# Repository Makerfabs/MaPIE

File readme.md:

# Makerfabs MaPIE

```c++
/*
Version:		V2.1
Author:			Vincent
Create Date:	2022/6/2
Note:

2022/12/30		V2.1 Edit wiki link
2022/11/23		V2.0 Add MaPIE 0.96 OLED
2022/6/2		V1.0 Create Project
			
*/
```

[toc]

# Makerfabs

[Makerfabs home page](https://www.makerfabs.com/)

[Makerfabs Wiki](https://wiki.makerfabs.com/)

# What is MaPIE 

MaPIE is Makerfabs development board product line based on RP2040.

RP2040 is an MCU developed by Raspberry PI and can support Arduino, MicroPython and C_SDK development.

Compared to the traditional Arduino UNO 328P, it has better performance and more hardware resources. 

## MaPIE List

| Name                                                         | Status      |
| ------------------------------------------------------------ | ----------- |
| [MaPIE LoRa RP2040](MaPIE_Lora/)                     | **Already** |
| [MaPIE 0.96 OLED](MaPIE-0.96-OLED/) | **Already** |
|                                                              |             |

# How To Use

## Complier Option

**If you have any questions，such as how to install the development board, how to download the code, how to install the library. Please refer to :[Makerfabs_FAQ](https://github.com/Makerfabs/Makerfabs_FAQ)**

- Please disconnect from the electrical equipment before burning!
- Do not burn with alternating current!
- Open Arduino IDE
- Open boards Manager, search "RP2040"
- Install board:  Arduino Mbed OS RP2040 Boards(Version 3.1.1)

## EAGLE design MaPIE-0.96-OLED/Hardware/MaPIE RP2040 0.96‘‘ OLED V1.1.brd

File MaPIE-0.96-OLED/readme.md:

# MaPIE RP2040 0.96‘‘ OLED

```c++
/*
Version:		V1.0
Author:			Vincent
Create Date:	2022/11/23
Note:
	
*/
```

[toc]

# Makerfabs

[Makerfabs home page](https://www.makerfabs.com/)

[Makerfabs Wiki](https://wiki.makerfabs.com/)

# MaPIE RP2040 0.96‘‘ OLED

## Intruduce

Product Link ：[MaPIE RP2040 0.96" OLED](https://www.makerfabs.com/mapie-rp2040-0-96-inch-oled.html) 

Wiki Link : [MaPIE RP2040 0.96" OLED](https://wiki.makerfabs.com/MaPIE_RP2040_0.96_OLED.html) 

This MaPIE RP2040 OLED is a low-cost, high-performance Pico-like MCU board with flexible digital interfaces. It is based on Raspberry Pi's RP2040 microcontroller chip, as same as that on Raspberry Pi Pico. Users can develop applications based on Raspberry Pi's C/C++ SDK, or the MicroPython/ Arduino.

## Feature

- P2040 microcontroller Dual-core Arm Cortex M0+ processor, flexible clock running up to 133 MHz
- 16MB on-board Flash memory
- USB-C connector
- 0.96" 128*64 OLED
- Lithium battery connector/ charge
- Same pins breakout as Pico: 26 x multi-function GPIO pins; 2 x SPI, 2 x I2C, 2 x UART, 3 x 12-bit ADC, 16 x controllable PWM channels

### Front:

### Back:

# Arduino

## Compiler Options

**If you have any questions，such as how to install the development board, how to download the code, how to install the library. Please refer to :[Makerfabs_FAQ](https://github.com/Makerfabs/Makerfabs_FAQ)**

- Install board : Arduino Mbed OS RP2040 Boards
- Install library : Adafruit_GFX library.
- Install library : Adafruit_SSD1306 library.

Modify pins_Arduino.h

```c++
//variants\RASPBERRY_PI_PICO\pins_arduino.h

// Wire
// #define PIN_WIRE_SDA        (4u)
// #define PIN_WIRE_SCL        (5u)

// Change By Vincent
#define PIN_WIRE_SDA        (6u)
#define PIN_WIRE_SCL        (7u)
```

**First time upload need hold boot button when restart.**

# MicroPython

## Burn Fireware

Download MicroPython from the Raspberry PI Pico's official tutorial:

[https://www.raspberrypi.com/products/raspberry-pi-pico/](https://www.raspberrypi.com/products/raspberry-pi-pico/)

## Upload Code

Connect MaPie to PC.

Use Thonny IDE, upload all file to MaPie.

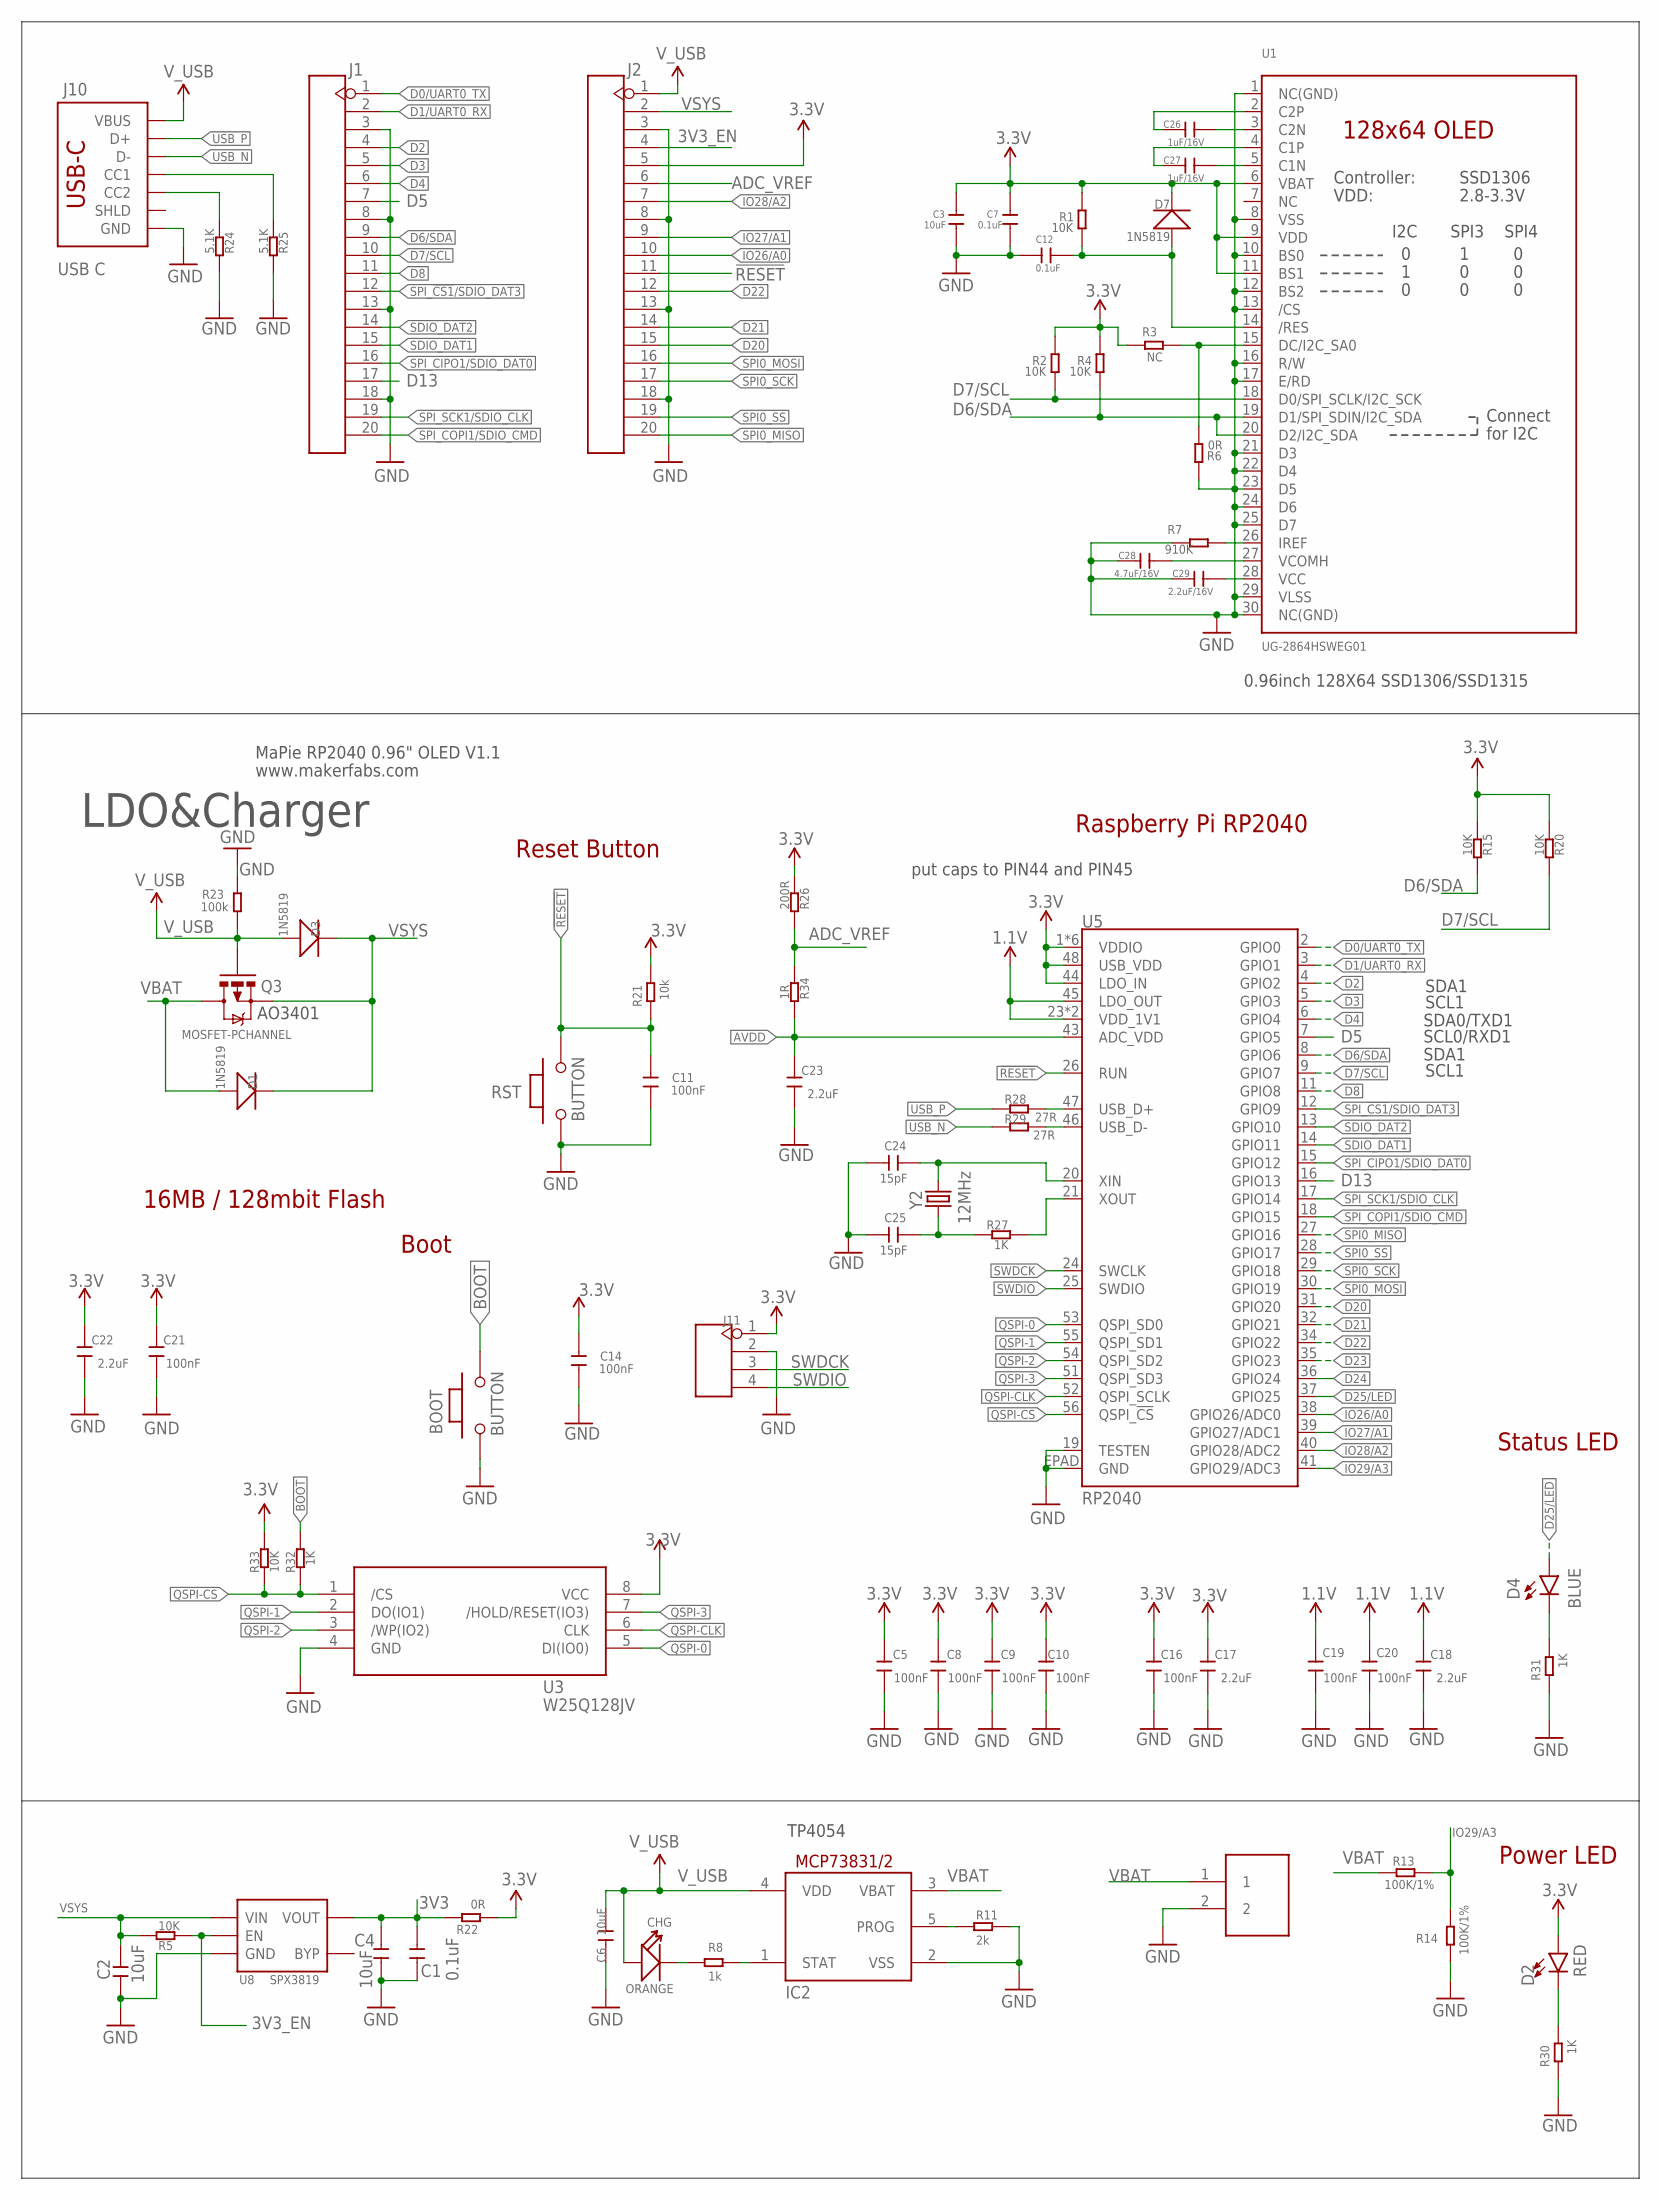
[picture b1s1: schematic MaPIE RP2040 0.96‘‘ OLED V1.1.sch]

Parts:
BAT: PH2.0-2P-90-DIP
BOOT: BUTTON; 157SW
C1, C7, C12: 0.1uF; C0603
C2, C3, C4, C6: 10uF; C0603
C5, C8, C9, C10, C11, C14, C16, C19, C20, C21: 100nF; C0603
C17, C18, C22, C23: 2.2uF; C0603
C24, C25: 15pF; C0603
C26, C27: 1uF/16V; C0603
C28: 4.7uF/16V; C0603
C29: 2.2uF/16V; C0603
CHG: ORANGE; D0603
D1, D3, D7: 1N5819; SOD323
D2: RED; LED-0603
D4: BLUE; LED-0603
IC2: MCP73831/OT; SOT23-5L
J1, J2: HEADER-20P-2.54; 20P-2.54
J10: USB C; USB-C-16P-4LAYER-ISOLATED
J11: HEADER-4P-60/35MILROUND; 4P-65/35ROUND
Q3: MOSFET-PCHANNEL; SOT23-3
R1, R2, R4, R5, R15, R20, R33: 10K; 0603
R3: NC; 0603
R6, R22: 0R; 0603
R7: 910K; 0603
R8: 1k; 0603
R11: 2k; 0603
R13, R14: 100K/1%; 0603
R21: 10k; 0603
R23: 100k; 0603
R24, R25: 5.1K; 0603
R26: 200R; 0603
R27, R30, R31, R32: 1K; 0603
R28, R29: 27R; 0603
R34: 1R; 0603
RST: BUTTON; 157SW
U1: UG-2864HSWEG01; UG-2864HSWEG01_0.96IN_WRAPAROUND
U3: W25Q128JV; SOIC-8-208MIL
U5: RP2040; QFN-56
U8: SPX3819; SOT23-5
Y2: 12MHz; CRYSTAL-SMD-2X2.5MM

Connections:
1.1V: C18.2, C19.2, C20.2, U5.23 (VDD_1V1), U5.45 (LDO_OUT), U5.50 (VDD_1V1)
3.3V: C3.1, C5.2, C7.1, C8.2, C9.2, C10.2, C14.2, C16.2, C17.2, C21.2, C22.2, D2.A, D7.-, J2.5, J11.1, R1.2, R2.2, R3.2, R4.2, R15.2, R20.2, R21.1, R22.1, R26.2, R33.1, U1.6 (VBAT), U1.9 (VDD), U1.11 (BS1), U3.8 (VCC), U5.1 (VDDIO), U5.10 (VDDIO), U5.22 (VDDIO), U5.33 (VDDIO), U5.42 (VDDIO), U5.44 (LDO_IN), U5.48 (USB_VDD), U5.49 (VDDIO)
3V3: C1.2, C4.2, R22.2, U8.5 (VOUT)
3V3_EN: J2.4, R5.2, U8.3 (EN)
!RESET!: C11.2, J2.11, R21.2, RST.2, U5.26 (RUN)
ADC_VREF: J2.6, R26.1, R34.2
AVDD: C23.2, R34.1, U5.43 (ADC_VDD)
BOOT: BOOT.2, R32.1
D0/UART0_TX: J1.1, U5.2 (GPIO0)
D1/UART0_RX: J1.2, U5.3 (GPIO1)
D2: J1.4, U5.4 (GPIO2)
D3: J1.5, U5.5 (GPIO3)
D4: J1.6, U5.6 (GPIO4)
D5: J1.7, U5.7 (GPIO5)
D6/SDA: J1.9, R4.1, R15.1, U1.19 (D1/SPI_SDIN/I2C_SDA), U1.20 (D2/I2C_SDA), U5.8 (GPIO6)
D7/SCL: J1.10, R2.1, R20.1, U1.18 (D0/SPI_SCLK/I2C_SCK), U5.9 (GPIO7)
D8: J1.11, U5.11 (GPIO8)
D13: J1.17, U5.16 (GPIO13)
D20: J2.15, U5.31 (GPIO20)
D21: J2.14, U5.32 (GPIO21)
D22: J2.12, U5.34 (GPIO22)
D23: U5.35 (GPIO23)
D24: U5.36 (GPIO24)
D25/LED: D4.A, U5.37 (GPIO25)
GND: BAT.2, BOOT.1, C1.1, C2.1, C3.2, C4.1, C5.1, C6.1, C7.2, C8.1, C9.1, C10.1, C11.1, C12.1, C14.1, C16.1, C17.1, C18.1, C19.1, C20.1, C21.1, C22.1, C23.1, C24.2, C25.2, C28.1, C29.1, IC2.2 (VSS), J1.3, J1.8, J1.13, J1.18, J2.3, J2.8, J2.13, J2.18, J10.GND, J10.GND2 (GND), J11.2, R6.2, R7.2, R11.2, R14.1, R23.2, R24.1, R25.1, R30.2, R31.2, RST.1, U1.1 (NC(GND)), U1.8 (VSS), U1.10 (BS0), U1.12 (BS2), U1.13 (/CS), U1.16 (R/W), U1.17 (E/RD), U1.21 (D3), U1.22 (D4), U1.23 (D5), U1.24 (D6), U1.25 (D7), U1.29 (VLSS), U1.30 (NC(GND)), U3.4 (GND), U5.19 (TESTEN), U5.EPAD (GND), U8.2 (GND)
IO26/A0: J2.10, U5.38 (GPIO26/ADC0)
IO27/A1: J2.9, U5.39 (GPIO27/ADC1)
IO28/A2: J2.7, U5.40 (GPIO28/ADC2)
IO29/A3: R13.1, R14.2, U5.41 (GPIO29/ADC3)
unnamed: C24.1, U5.20 (XIN), Y2.P3 (2)
unnamed: D4.C, R31.1
unnamed: R3.1, R6.1, U1.15 (DC/I2C_SA0)
unnamed: R27.1, U5.21 (XOUT)
unnamed: C28.2, U1.27 (VCOMH)
unnamed: C25.1, R27.2, Y2.P1 (1)
unnamed: D2.C, R30.1
unnamed: C29.2, U1.28 (VCC)
unnamed: R7.1, U1.26 (IREF)
unnamed: C26.2, U1.3 (C2N)
unnamed: J10.A5 (CC1), R25.2
unnamed: J10.B5 (CC2), R24.2
unnamed: C26.1, U1.2 (C2P)
unnamed: C27.1, U1.4 (C1P)
unnamed: C27.2, U1.5 (C1N)
unnamed: C12.2, D7.+, R1.1, U1.14 (/RES)
unnamed: CHG.-, R8.1
unnamed: IC2.1 (STAT), R8.2
unnamed: IC2.5 (PROG), R11.1
QSPI-0: U3.5 (DI(IO0)), U5.53 (QSPI_SD0)
QSPI-1: U3.2 (DO(IO1)), U5.55 (QSPI_SD1)
QSPI-2: U3.3 (/WP(IO2)), U5.54 (QSPI_SD2)
QSPI-3: U3.7 (/HOLD/RESET(IO3)), U5.51 (QSPI_SD3)
QSPI-CLK: U3.6 (CLK), U5.52 (QSPI_SCLK)
QSPI-CS: R32.2, R33.2, U3.1 (/CS), U5.56 (QSPI_!CS!)
SDIO_DAT1: J1.15, U5.14 (GPIO11)
SDIO_DAT2: J1.14, U5.13 (GPIO10)
SPI0_MISO: J2.20, U5.27 (GPIO16)
SPI0_MOSI: J2.16, U5.30 (GPIO19)
SPI0_SCK: J2.17, U5.29 (GPIO18)
SPI0_SS: J2.19, U5.28 (GPIO17)
SPI_!CS1!/SDIO_DAT3: J1.12, U5.12 (GPIO9)
SPI_CIPO1/SDIO_DAT0: J1.16, U5.15 (GPIO12)
SPI_COPI1/SDIO_CMD: J1.20, U5.18 (GPIO15)
SPI_SCK1/SDIO_CLK: J1.19, U5.17 (GPIO14)
SWDCK: J11.3, U5.24 (SWCLK)
SWDIO: J11.4, U5.25 (SWDIO)
USB_F_N: R29.1, U5.46 (USB_D-)
USB_F_P: R28.1, U5.47 (USB_D+)
USB_N: J10.A7 (D-), J10.B7 (D-), R29.2
USB_P: J10.A6 (D+), J10.B6 (D+), R28.2
VBAT: BAT.1, D1.+, IC2.3 (VBAT), Q3.3 (D), R13.2
VSYS: C2.2, D1.-, D3.-, J2.2, Q3.2 (S), R5.1, U8.1 (VIN)
V_USB: C6.2, CHG.+, D3.+, IC2.4 (VDD), J2.1, J10.VBUS1 (VBUS), J10.VBUS2 (VBUS), Q3.1 (G), R23.1

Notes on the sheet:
MaPie RP2040 0.96" OLED V1.1
www.makerfabs.com
TP4054
16MB / 128mbit Flash
Raspberry Pi RP2040
Reset Button
Status LED
Boot
Power LED
put caps to PIN44 and PIN45
SDA0/TXD1
SCL0/RXD1
SDA1
SCL1
LDO&Charger
AO3401
0.96inch 128X64 SSD1306/SSD1315

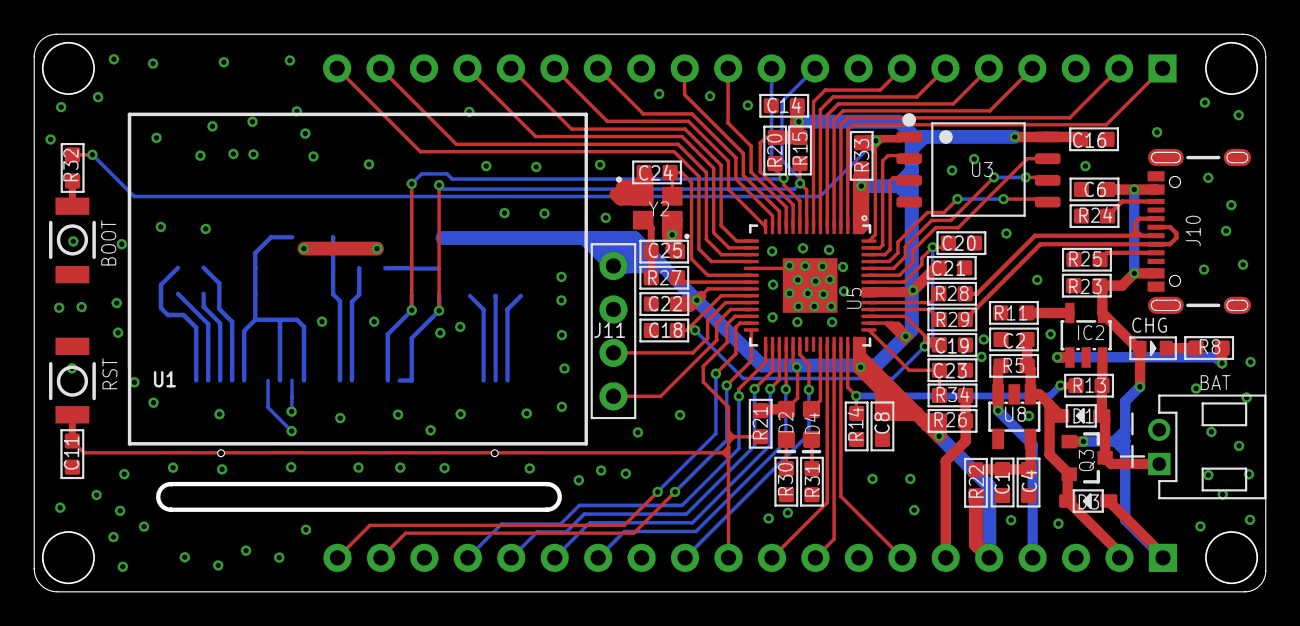
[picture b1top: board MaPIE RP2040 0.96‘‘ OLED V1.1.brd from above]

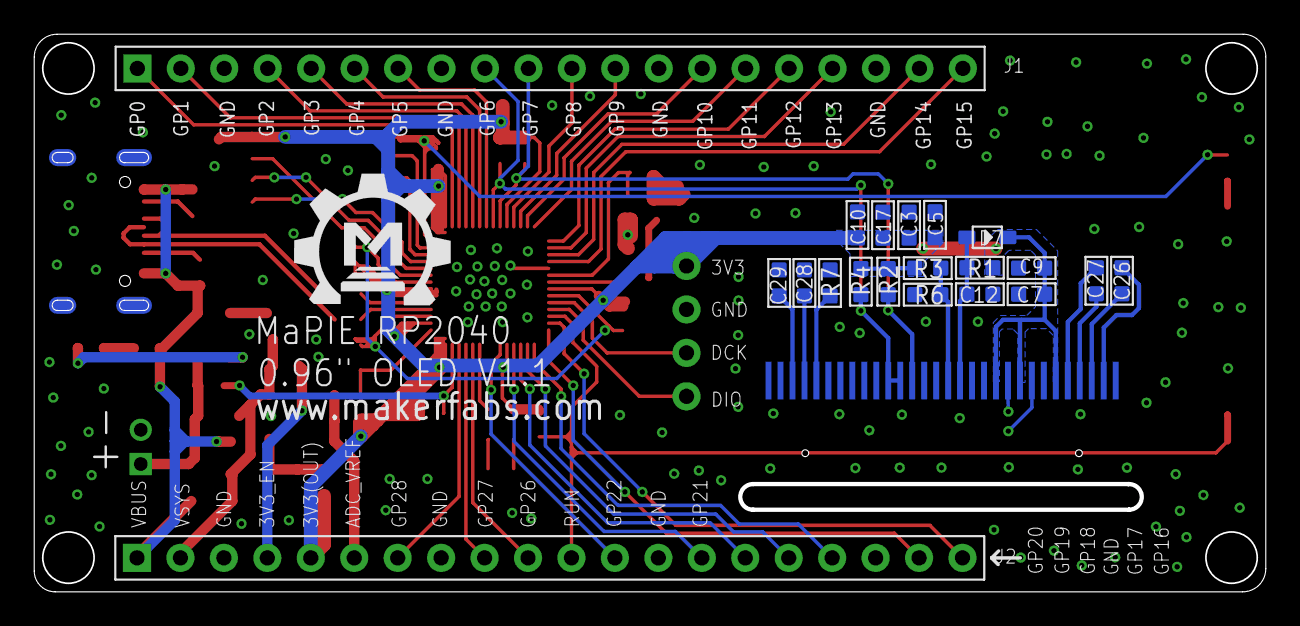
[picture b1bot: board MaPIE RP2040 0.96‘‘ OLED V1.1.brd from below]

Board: 2 copper layers, 71.7 x 32.3 mm, 75 parts (21 on the bottom side), 71 nets.

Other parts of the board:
U$1: MAKERFABS_0.3

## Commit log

2022-06-02 Create Project.
2022-06-05 Add compiled firmware
2022-06-16 Add MaPIE lora hardware
2022-11-23 Add MaPIE 0.96 OLED
2022-11-23 Edit Readme
2022-11-29 hardware
    v1.1
2022-12-30 Edit readme.

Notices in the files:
parts and their libraries:
SparkFun-Connectors: Licensing: Creative Commons ShareAlike 4.0 International - https://creativecommons.org/licenses/by-sa/4.0
